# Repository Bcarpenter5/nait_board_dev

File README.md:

# nait_board_dev
> Owner : Brandon Carpenter
> Class : cmp2750

## link to chip on digikey 
[stm32G031K8t6](https://www.digikey.ca/en/products/detail/stmicroelectronics/STM32G031K8T6/10300267)

### the usb device on jlcpcb
> MINI 5PTP

> Note - now sent in and finished

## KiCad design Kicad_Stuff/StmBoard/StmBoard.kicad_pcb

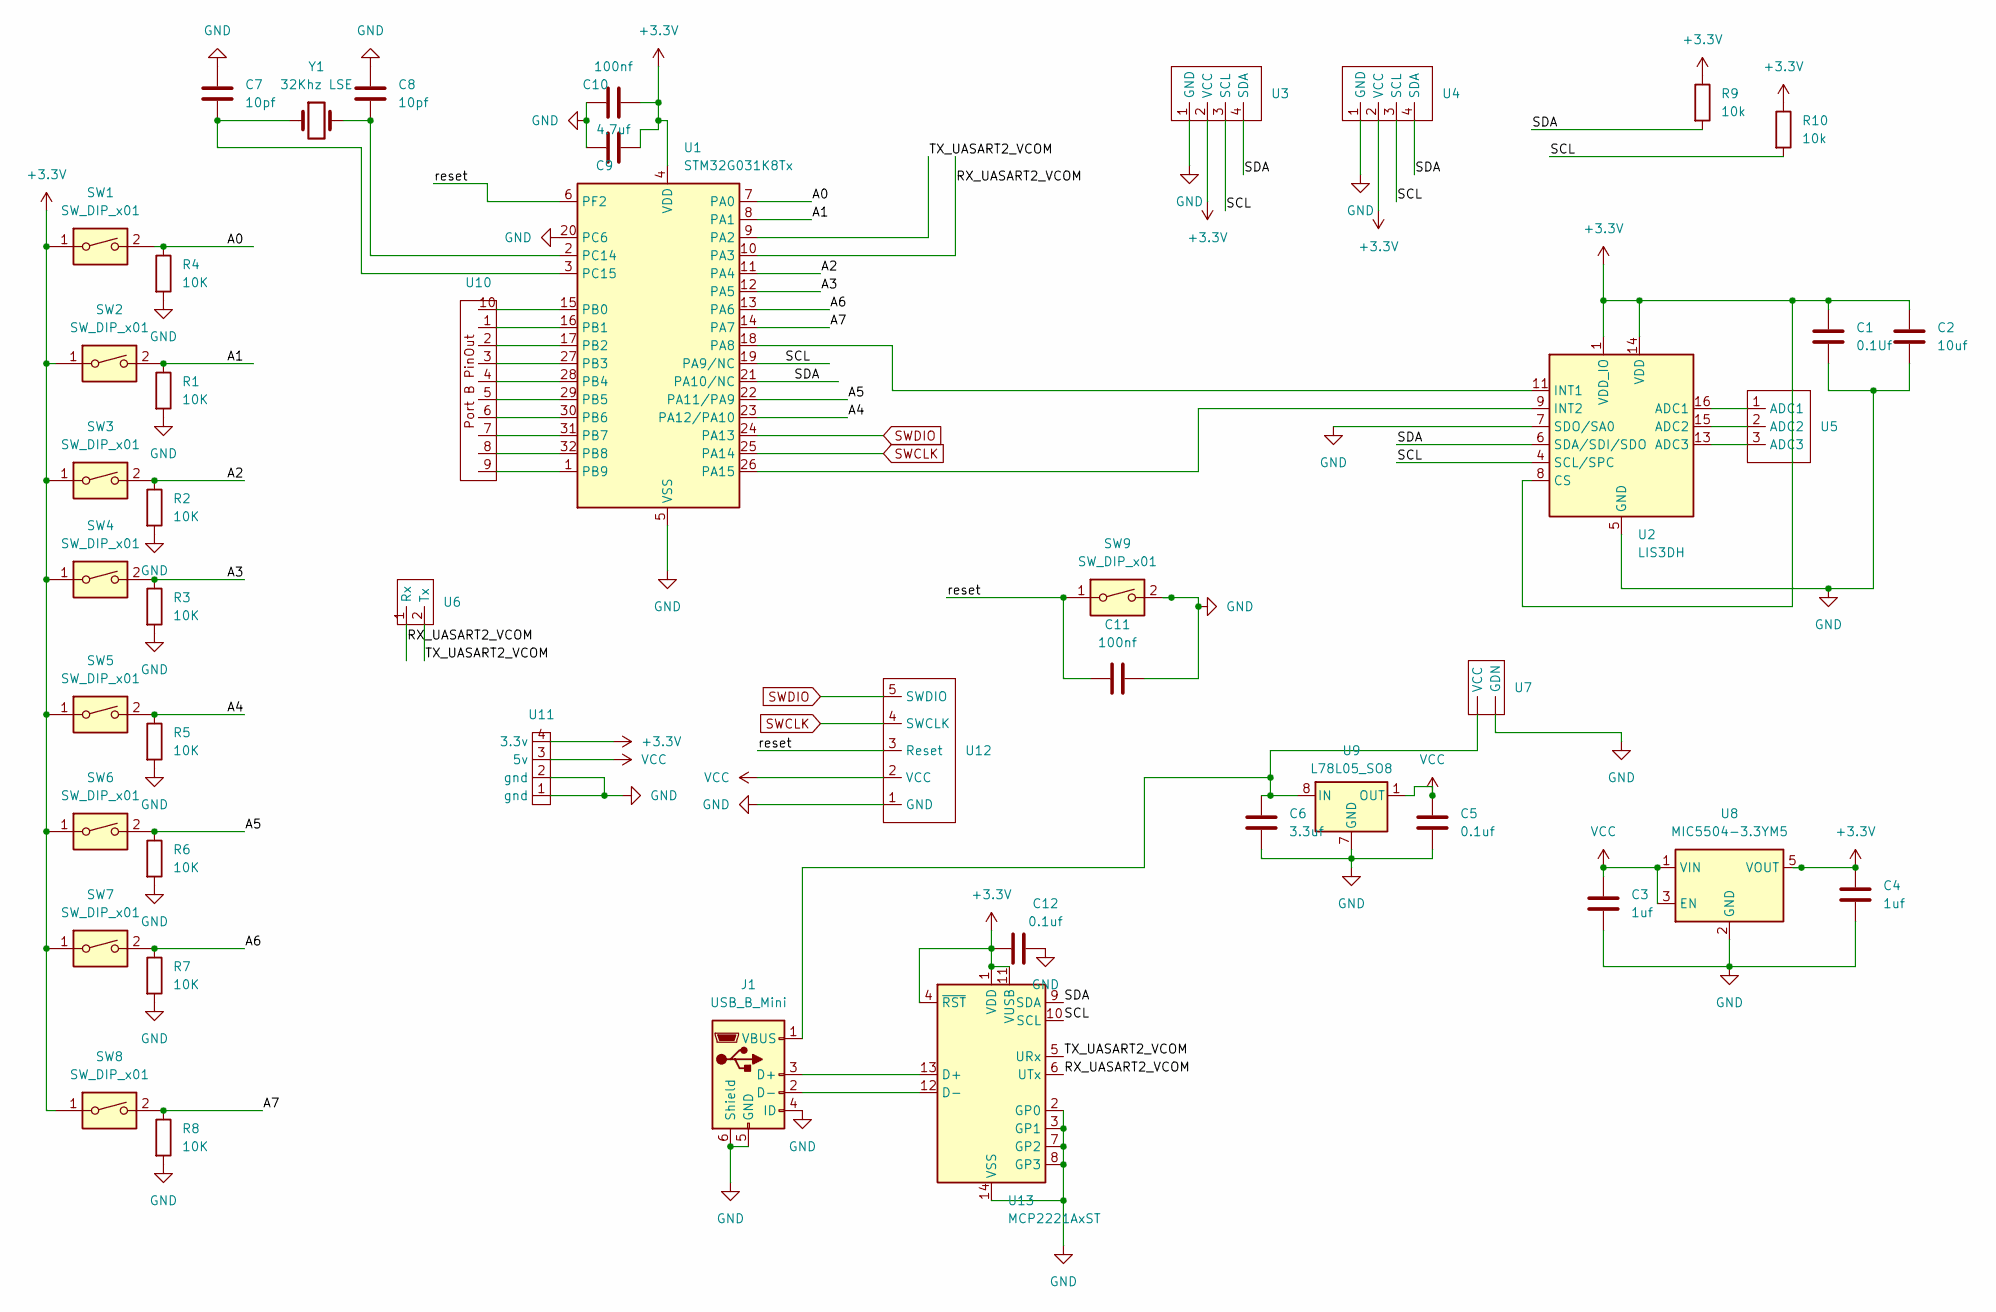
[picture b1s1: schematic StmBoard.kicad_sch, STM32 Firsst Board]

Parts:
C1: 0.1Uf; C_0805_2012Metric
C2: 10uf; C_0805_2012Metric
C3, C4: 1uf; C_0805_2012Metric
C5, C12: 0.1uf; C_0805_2012Metric
C6: 3.3uf; C_0805_2012Metric
C7, C8: 10pf; C_0805_2012Metric
C9: 4.7uf; C_0805_2012Metric
C10, C11: 100nf; C_0805_2012Metric
J1: USB_B_Mini; USB_Mini-B_Lumberg_2486_01_Horizontal
R1, R2, R3, R4, R5, R6, R7, R8: 10K; R_0603_1608Metric
R9, R10: 10k; R_0603_1608Metric
SW1, SW2, SW3, SW4, SW5, SW6, SW7, SW8, SW9: SW_DIP_x01; SW_PUSH_6mm
U1: STM32G031K8Tx; LQFP-32_7x7mm_P0.8mm
U2: LIS3DH; LGA-16_3x3mm_P0.5mm_LayoutBorder3x5y
U3, U4, U11: PinHeader_1x04_P2.54mm_Vertical
U5: PinHeader_1x03_P2.54mm_Vertical
U6, U7: PinHeader_1x02_P2.54mm_Vertical
U8: MIC5504-3.3YM5; SOT-23-5
U9: L78L05_SO8; SOIC-8_3.9x4.9mm_P1.27mm
U10: PinSocket_1x10_P2.54mm_Vertical
U12: PinHeader_1x05_P2.54mm_Vertical
U13: MCP2221AxST; TSSOP-14_4.4x5mm_P0.65mm
Y1: 32Khz LSE; Crystal_SMD_3215-2Pin_3.2x1.5mm

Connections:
+3.3V: C1.1, C2.1, C4.1, C9.2, C10.2, C12.1, R9.1, R10.1, SW1.1, SW2.1, SW3.1, SW4.1, SW5.1, SW6.1, SW7.1, SW8.1, U1.4 (VDD), U2.1 (VDD_IO), U2.8 (CS), U2.14 (VDD), U3.2 (VCC), U4.2 (VCC), U8.5 (VOUT), U11.4 (3.3v), U13.1 (VDD), U13.4 (~RST), U13.11 (VUSB)
/A0: R4.1, SW1.2, U1.7 (PA0)
/A1: R1.1, SW2.2, U1.8 (PA1)
/A2: R2.1, SW3.2, U1.11 (PA4)
/A3: R3.1, SW4.2, U1.12 (PA5)
/A4: R5.1, SW5.2, U1.23 (PA12/PA10)
/A5: R6.1, SW6.2, U1.22 (PA11/PA9)
/A6: R7.1, SW7.2, U1.13 (PA6)
/A7: R8.1, SW8.2, U1.14 (PA7)
/RX_UASART2_VCOM: U1.10 (PA3), U6.1 (Rx), U13.6 (UTx)
/SCL: R10.2, U1.19 (PA9/NC), U2.4 (SCL/SPC), U3.3 (SCL), U4.3 (SCL), U13.10 (SCL)
/SDA: R9.2, U1.21 (PA10/NC), U2.6 (SDA/SDI/SDO), U3.4 (SDA), U4.4 (SDA), U13.9 (SDA)
/TX_UASART2_VCOM: U1.9 (PA2), U6.2 (Tx), U13.5 (URx)
/reset: C11.2, SW9.1, U1.6 (PF2), U12.3 (Reset)
GND: C1.2, C2.2, C3.2, C4.2, C5.2, C6.2, C7.1, C8.1, C9.1, C10.1, C11.1, C12.2, J1.4 (ID), J1.5 (GND), J1.6 (Shield), R1.2, R2.2, R3.2, R4.2, R5.2, R6.2, R7.2, R8.2, SW9.2, U1.5 (VSS), U1.20 (PC6), U2.5 (GND), U2.7 (SDO/SA0), U2.10 (GND), U2.12 (GND), U3.1 (GND), U4.1 (GND), U7.2 (GDN), U8.2 (GND), U9.2 (GND), U9.3 (GND), U9.6 (GND), U9.7 (GND), U11.1 (gnd), U11.2 (gnd), U12.1 (GND), U13.2 (GP0), U13.3 (GP1), U13.7 (GP2), U13.8 (GP3), U13.14 (VSS)
unnamed: J1.3 (D+), U13.13 (D+)
unnamed: J1.2 (D-), U13.12 (D-)
unnamed: C6.1, J1.1 (VBUS), U7.1 (VCC), U9.8 (IN)
unnamed: U1.18 (PA8), U2.11 (INT1)
unnamed: U1.26 (PA15), U2.9 (INT2)
unnamed: U1.15 (PB0), U10.10 (PB_0)
unnamed: U1.16 (PB1), U10.1 (PB_1)
unnamed: U1.17 (PB2), U10.2 (PB_2)
unnamed: U1.27 (PB3), U10.3 (PB_3)
unnamed: U1.28 (PB4), U10.4 (PB_4)
unnamed: U1.29 (PB5), U10.5 (PB_5)
unnamed: U1.30 (PB6), U10.6 (PB_6)
unnamed: U1.31 (PB7), U10.7 (PB_7)
unnamed: U1.32 (PB8), U10.8 (PB_8)
unnamed: U1.1 (PB9), U10.9 (PB_9)
unnamed: C8.2, U1.2 (PC14), Y1.2
unnamed: C7.2, U1.3 (PC15), Y1.1
unnamed: U2.16 (ADC1), U5.1 (ADC1)
unnamed: U2.15 (ADC2), U5.2 (ADC2)
unnamed: U2.13 (ADC3), U5.3 (ADC3)
SWCLK: U1.25 (PA14), U12.4 (SWCLK)
SWDIO: U1.24 (PA13), U12.5 (SWDIO)
VCC: C3.1, C5.1, U8.1 (VIN), U8.3 (EN), U9.1 (OUT), U11.3 (5v), U12.2 (VCC)

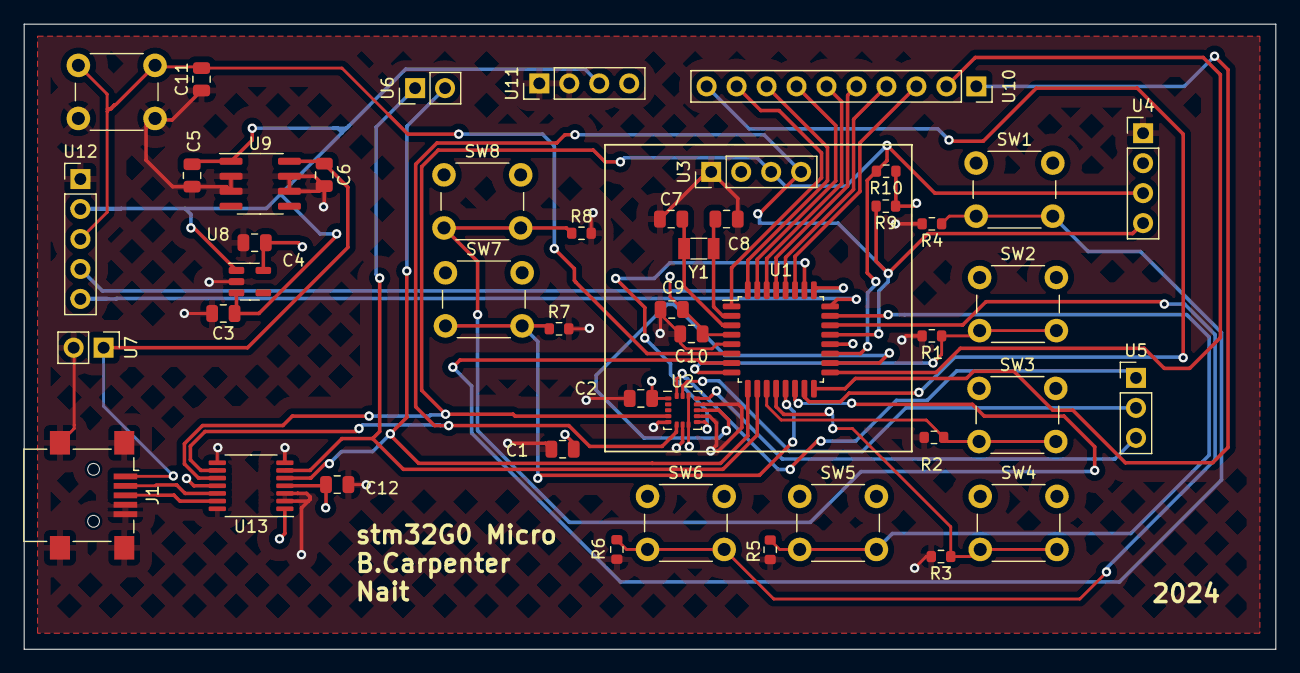
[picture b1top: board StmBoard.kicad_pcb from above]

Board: 4 copper layers, 106.1 x 53.0 mm, 46 parts (0 on the bottom side), 38 nets.

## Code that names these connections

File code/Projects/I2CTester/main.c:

#include "stm32g031xx.h"
#include <stdio.h>

#include "clock.h"
#include "gpio.h"
#include "I2C.h"
#include "ssd1306.h"

/*************************** Defines ****************************/
// nuclio board has an external led on pin d6/pc_6
#define LED_PIN 6
// this pin is connected to the external led
#define D9 8 
#define PA8 D9
// this pin is connected to a button
#define A0 0 
#define PA0 A0
// set pin d5/pa_9 is scl
#define D4 10
#define PA10 D4
// set pin d4/pa_10 is sda
#define D5 9
#define PA9 D5



/*************************** Globals ****************************/

/*************************** main function ****************************/
int main(void) {
    __enable_irq();
    ClockSet(_16MHz);
    printf("clock : %d\n", SystemCoreClock);
    TimerInit();
    // I2C_init();

    // GPIO init manual version for testing purposes
    GPIO_InitAlternateF(GPIOA, 9, 6); // set pin d5/pa_9 is scl
    GPIOA->OTYPER |= (1 << 9); // set pin d5/pa_9 is open drain
    GPIOA->OSPEEDR |= (3 << 18); // set pin d5/pa_9 is high speed
    GPIO_InitAlternateF(GPIOA, 10, 6); // set pin d4/pa_10 is sda
    GPIOA->OTYPER |= (1 << 10); // set pin d4/pa_10 is open drain
    GPIOA->OSPEEDR |= (3 << 20); // set pin d4/pa_10 is high speed

    RCC->APBENR1 |= RCC_APBENR1_I2C1EN; // Enable clock for I2C1

    I2C1->CR1 &= ~I2C_CR1_PE; // Disable I2C1
                              //
    // the settings for 100kHz on a 16MHz clock
    uint32_t presc = 0x3 << I2C_TIMINGR_PRESC_Pos;
    uint32_t scll = 0x13 << I2C_TIMINGR_SCLL_Pos;
    uint32_t sclh = 0xF << I2C_TIMINGR_SCLH_Pos;
    uint32_t sdadel = 0x2 << I2C_TIMINGR_SDADEL_Pos;
    uint32_t scldel = 0x4 << I2C_TIMINGR_SCLDEL_Pos;
    I2C1->TIMINGR = scll | sclh | sdadel | scldel | presc;


    I2C1->CR2 |= I2C_CR2_HEAD10R; // 10 bit addressing mode

    // now enable the I2C1 peripheral
    I2C1->CR1 |= I2C_CR1_PE; // Enable I2C1

    // pins already configured in main.c
    //ssd1306_Init();
    //ssd1306_DrawPixel(10,10,White);
   //ssd1306_UpdateScreen();
    
    
    // I2C_address(I2C1, 0x79, I2C_READ);
    //

    // set the adress of the slave
    I2C_TypeDef *I2Cx = I2C1;
    uint32_t adress = (0x3C);
    uint32_t rw = I2C_WRITE;



    // I2C_address(I2C1, 0x79, I2C_WRITE);
    printf("entering the Main loop\n");
    ssd1306_Init();



    ssd1306_SetCursor(12, 25);
    ssd1306_WriteString("Get Ligma", Font_11x18, White);
    ssd1306_UpdateScreen();





    char data = 56;

/*************************** main loop ****************************/
    while(1) {// loop forever

    DelayMs(1000);


    }
}
/*************************** Functions ****************************/

/*************************** Interrupts ****************************/


/*************************** End of file ****************************/

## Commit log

2024-01-16 quick commit
2024-03-26 Sent the board in to be manufacctured
2024-04-17 added the user manual
2024-04-17 I added all code and libraries to the repositiry for more up to date view official code repo
